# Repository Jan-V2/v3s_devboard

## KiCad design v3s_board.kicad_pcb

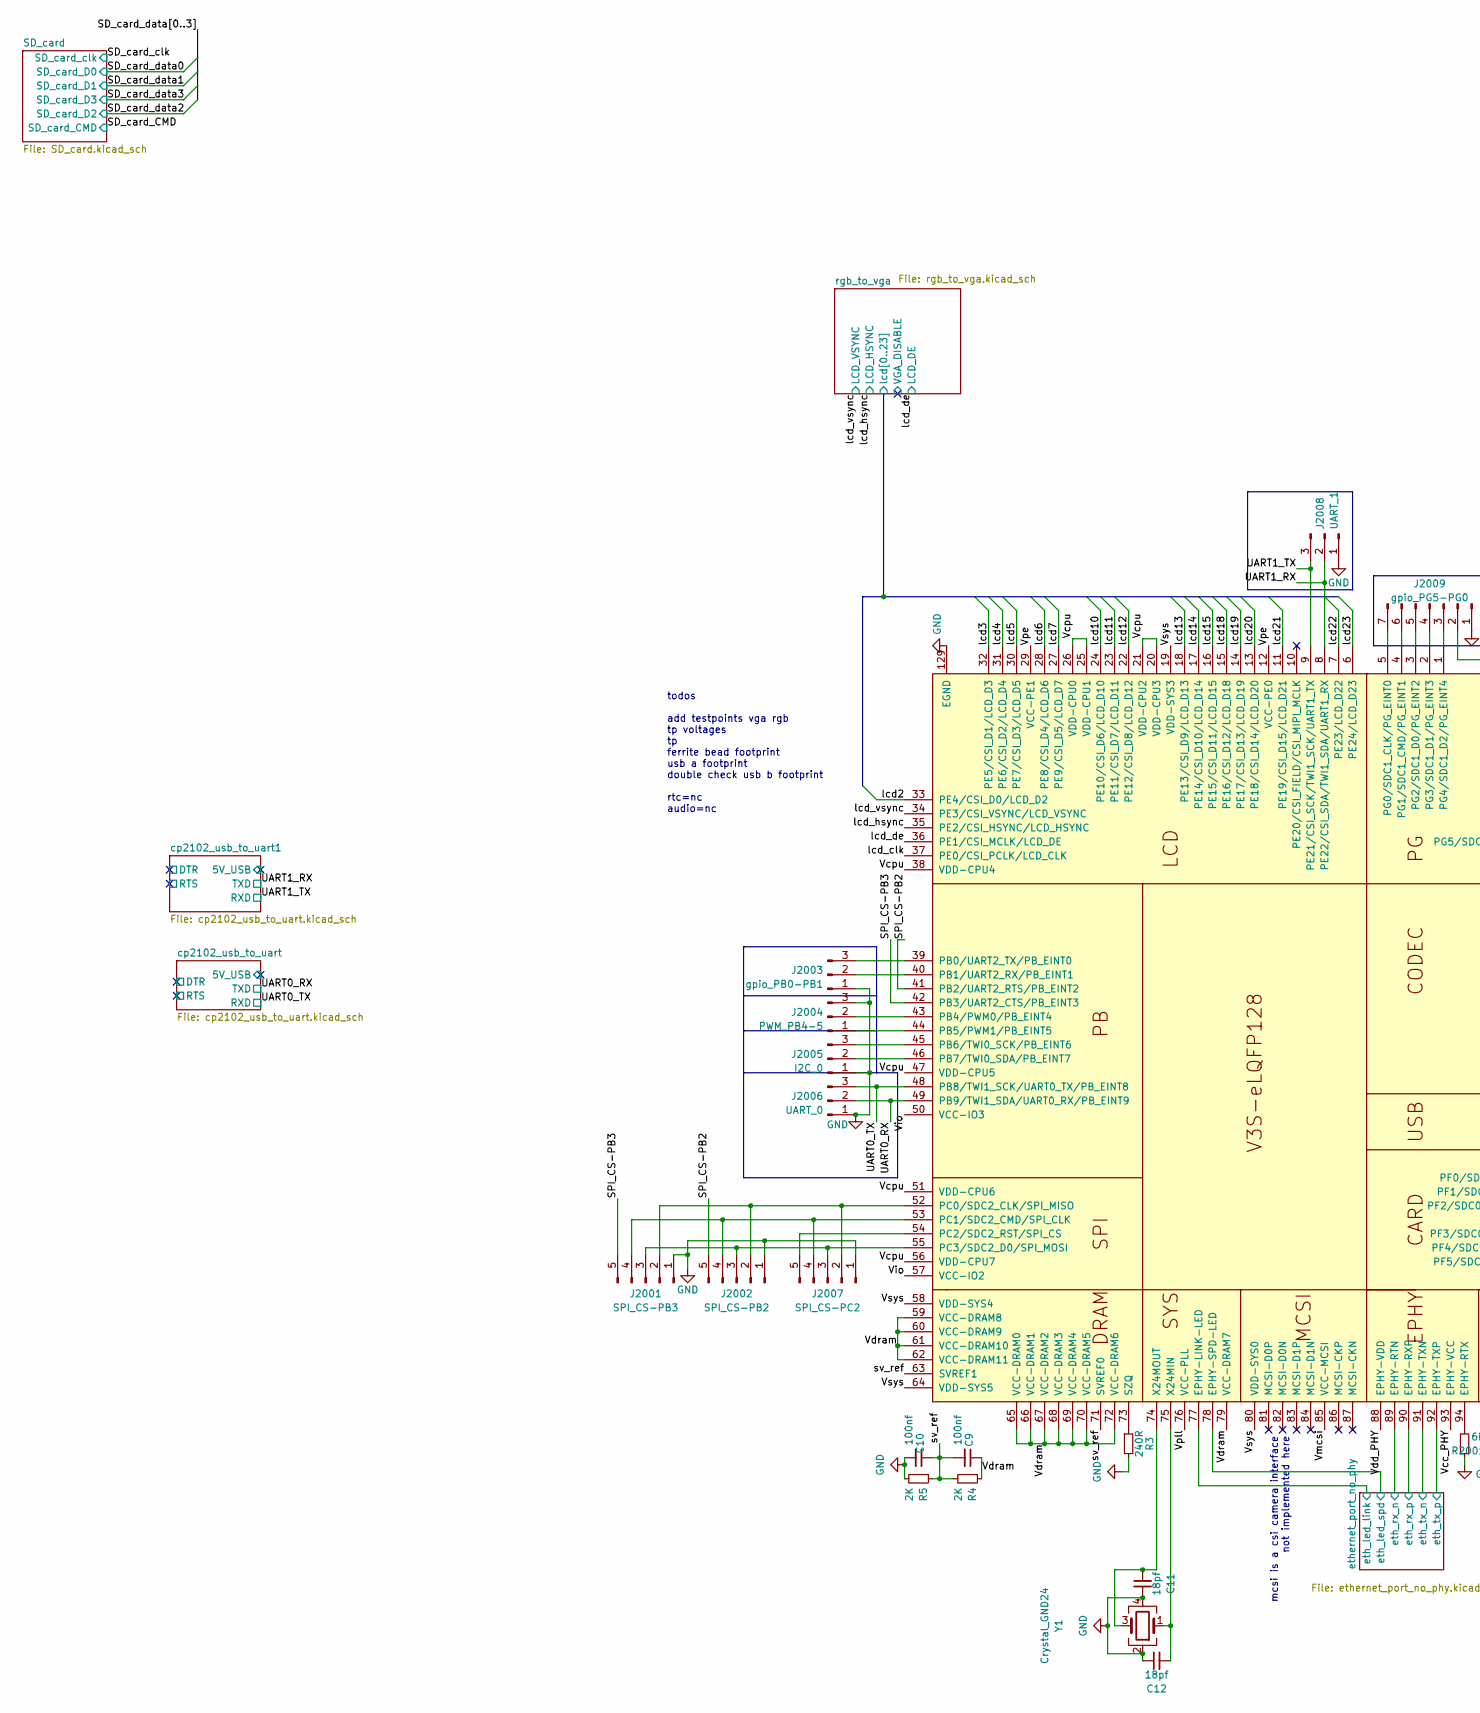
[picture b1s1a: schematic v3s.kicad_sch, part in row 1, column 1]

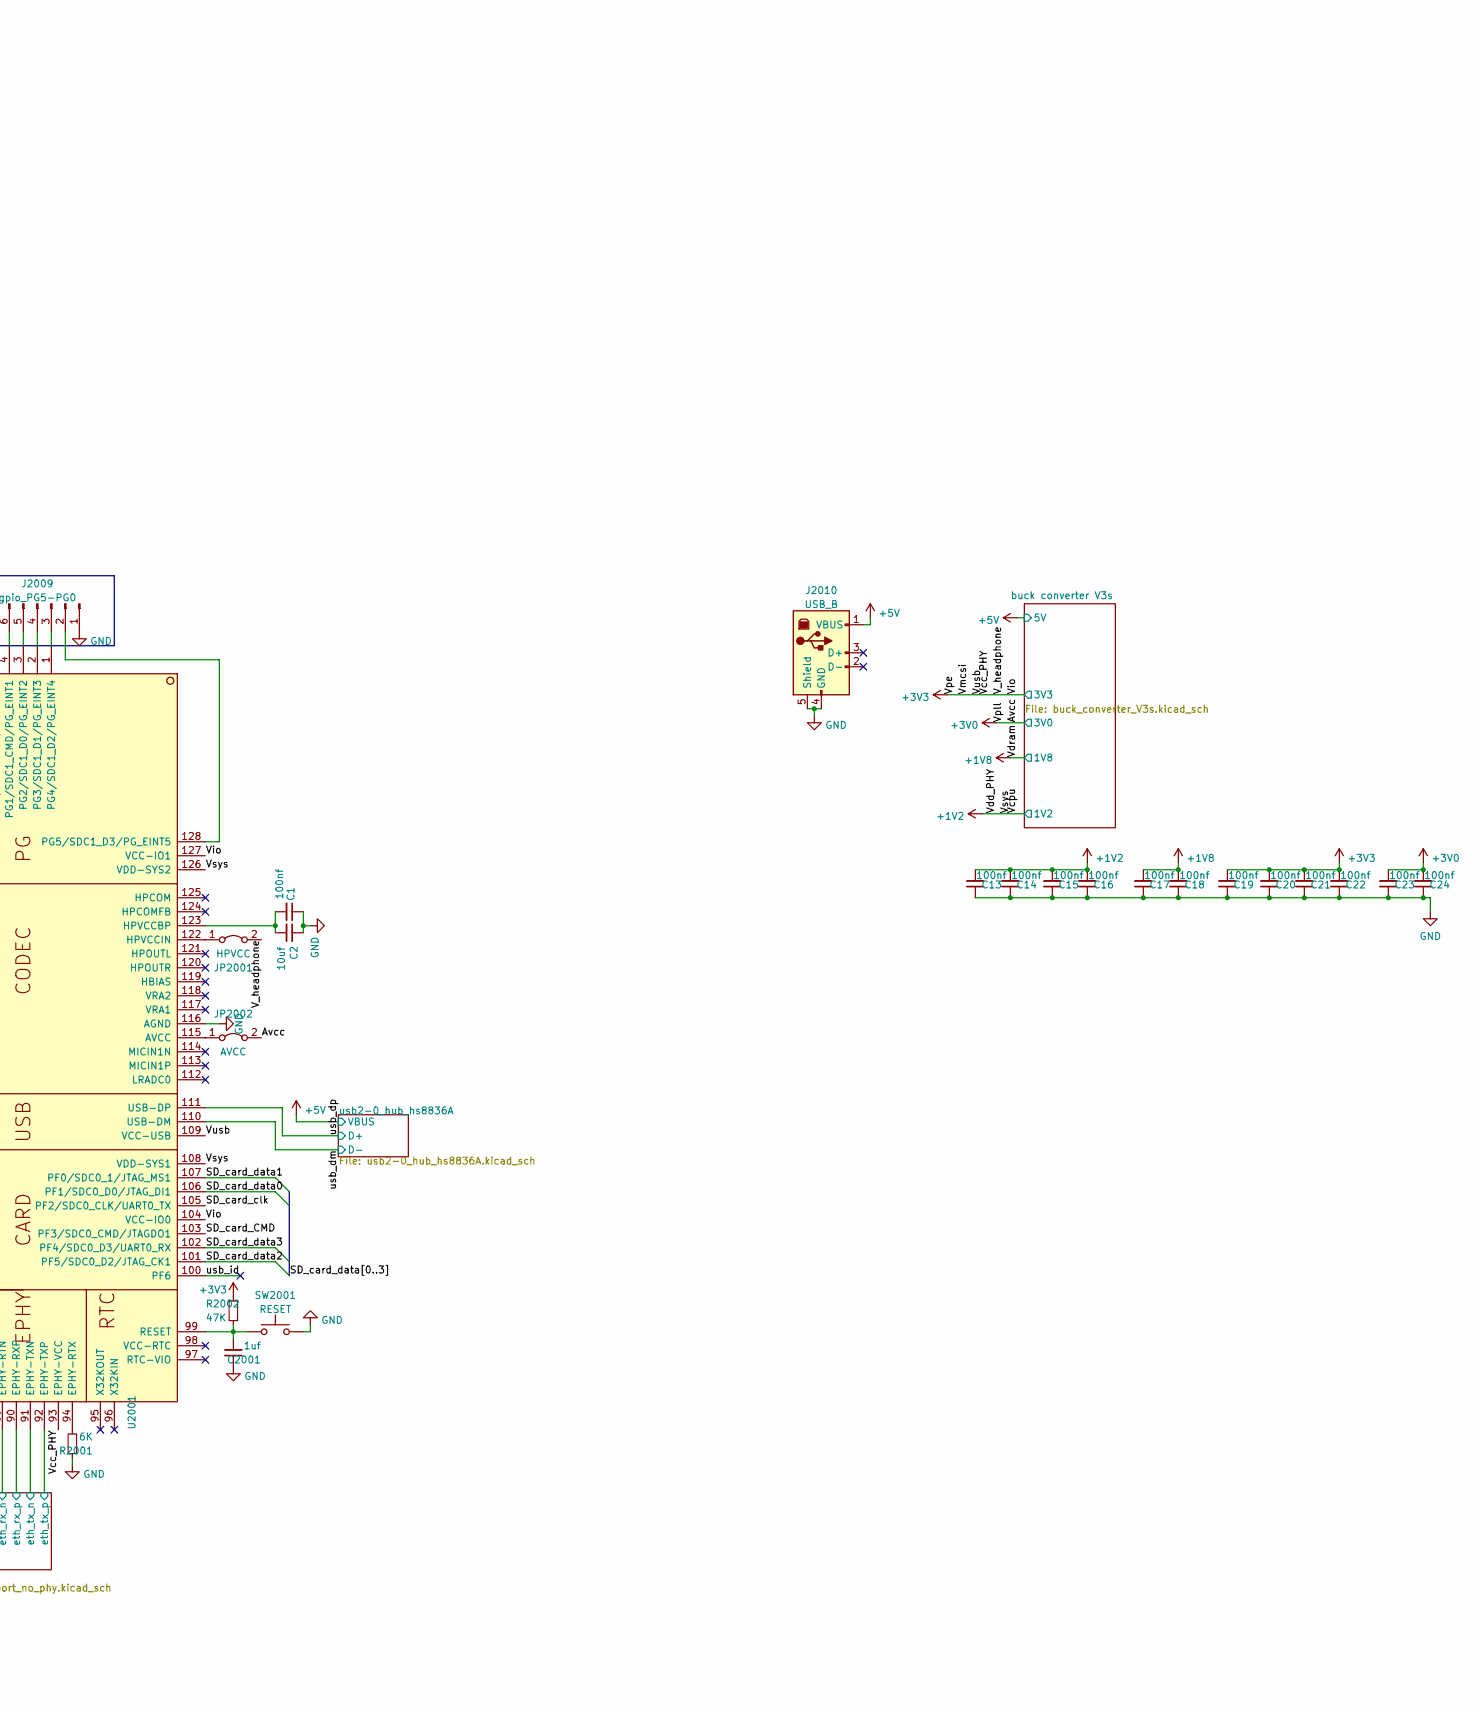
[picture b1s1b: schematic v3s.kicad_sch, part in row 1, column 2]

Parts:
C1, C9, C10, C13, C14, C15, C16, C17, C18, C19, C20, C21, C22, C23, C24: 100nf; C_0603_1608Metric
C2: 10uf; C_0603_1608Metric
C11, C12: 18pf; C_0603_1608Metric
C2001: 1uf; C_0603_1608Metric
J2001: SPI_CS-PB3; PinHeader_1x05_P2.54mm_Vertical
J2002: SPI_CS-PB2; PinHeader_1x05_P2.54mm_Vertical
J2003: gpio_PB0-PB1; PinHeader_1x03_P2.54mm_Vertical
J2004: PWM_PB4-5; PinHeader_1x03_P2.54mm_Vertical
J2005: I2C_0; PinHeader_1x03_P2.54mm_Vertical
J2006: UART_0; PinHeader_1x03_P2.54mm_Vertical
J2007: SPI_CS-PC2; PinHeader_1x05_P2.54mm_Vertical
J2008: UART_1; PinHeader_1x03_P2.54mm_Vertical
J2009: gpio_PG5-PG0; PinHeader_1x07_P2.54mm_Vertical
J2010: USB_B; USB_B_TE_5787834_Vertical
JP2001: HPVCC; SolderJumper-2_P1.3mm_Bridged_Pad1.0x1.5mm
JP2002: AVCC; SolderJumper-2_P1.3mm_Bridged_Pad1.0x1.5mm
R3: 240R; R_0603_1608Metric
R4, R5: 2K; R_0603_1608Metric
R2001: 6K; R_0603_1608Metric
R2002: 47K; R_0603_1608Metric
SW2001: RESET; SW_PUSH_6mm
U2001: V3S; LQFP-128_14x14mm_P0.4mm
Y1: Crystal_GND24; Crystal_SMD_3225-4Pin_3.2x2.5mm_HandSoldering

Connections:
+1V2: C13.2, C14.2, C15.2, C16.2, U2001.19 (VDD-SYS3), U2001.20 (VDD-CPU3), U2001.21 (VDD-CPU2), U2001.25 (VDD-CPU1), U2001.26 (VDD-CPU0), U2001.38 (VDD-CPU4), U2001.47 (VDD-CPU5), U2001.51 (VDD-CPU6), U2001.56 (VDD-CPU7), U2001.58 (VDD-SYS4), U2001.64 (VDD-SYS5), U2001.80 (VDD-SYS0), U2001.88 (EPHY-VDD), U2001.108 (VDD-SYS1), U2001.126 (VDD-SYS2); also elsewhere on the board
+1V8: C9.1, C17.2, C18.2, R4.1, U2001.59 (VCC-DRAM8), U2001.60 (VCC-DRAM9), U2001.61 (VCC-DRAM10), U2001.62 (VCC-DRAM11), U2001.65 (VCC-DRAM0), U2001.66 (VCC-DRAM1), U2001.67 (VCC-DRAM2), U2001.68 (VCC-DRAM3), U2001.69 (VCC-DRAM4), U2001.70 (VCC-DRAM5), U2001.72 (VCC-DRAM6), U2001.79 (VCC-DRAM7); also elsewhere on the board
+3V0: C23.2, C24.2, JP2002.2 (B), U2001.76 (VCC-PLL); also elsewhere on the board
+3V3: C19.2, C20.2, C21.2, C22.2, JP2001.2 (B), R2002.1, U2001.12 (VCC-PE0), U2001.29 (VCC-PE1), U2001.50 (VCC-IO3), U2001.57 (VCC-IO2), U2001.85 (VCC-MCSI), U2001.93 (EPHY-VCC), U2001.104 (VCC-IO0), U2001.109 (VCC-USB), U2001.127 (VCC-IO1); also elsewhere on the board
+5V: J2010.1 (VBUS); also elsewhere on the board
/v3s/SD_card_CMD: U2001.103 (PF3/SDC0_CMD/JTAGDO1); also elsewhere on the board
/v3s/SD_card_clk: U2001.105 (PF2/SDC0_CLK/UART0_TX); also elsewhere on the board
/v3s/SD_card_data0: U2001.106 (PF1/SDC0_D0/JTAG_DI1); also elsewhere on the board
/v3s/SD_card_data1: U2001.107 (PF0/SDC0_1/JTAG_MS1); also elsewhere on the board
/v3s/SD_card_data2: U2001.101 (PF5/SDC0_D2/JTAG_CK1); also elsewhere on the board
/v3s/SD_card_data3: U2001.102 (PF4/SDC0_D3/UART0_RX); also elsewhere on the board
/v3s/SPI_CS-PB2: J2002.5, U2001.41 (PB2/UART2_RTS/PB_EINT2)
/v3s/SPI_CS-PB3: J2001.5, U2001.42 (PB3/UART2_CTS/PB_EINT3)
/v3s/UART0_RX: J2006.2, U2001.49 (PB9/TWI1_SDA/UART0_RX/PB_EINT9); also elsewhere on the board
/v3s/UART0_TX: J2006.3, U2001.48 (PB8/TWI1_SCK/UART0_TX/PB_EINT8); also elsewhere on the board
/v3s/UART1_RX: J2008.2, U2001.8 (PE22/CSI_SDA/TWI1_SDA/UART1_RX); also elsewhere on the board
/v3s/UART1_TX: J2008.3, U2001.9 (PE21/CSI_SCK/TWI1_SCK/UART1_TX); also elsewhere on the board
/v3s/ethernet_port_no_phy/eth_led_link: U2001.77 (EPHY-LINK-LED); also elsewhere on the board
/v3s/ethernet_port_no_phy/eth_led_spd: U2001.78 (EPHY-SPD-LED); also elsewhere on the board
/v3s/ethernet_port_no_phy/eth_rx_n: U2001.89 (EPHY-RTN); also elsewhere on the board
/v3s/ethernet_port_no_phy/eth_rx_p: U2001.90 (EPHY-RXP); also elsewhere on the board
/v3s/ethernet_port_no_phy/eth_tx_n: U2001.91 (EPHY-TXN); also elsewhere on the board
/v3s/ethernet_port_no_phy/eth_tx_p: U2001.92 (EPHY-TXP); also elsewhere on the board
/v3s/lcd_clk: U2001.37 (PE0/CSI_PCLK/LCD_CLK)
/v3s/lcd_de: U2001.36 (PE1/CSI_MCLK/LCD_DE); also elsewhere on the board
/v3s/lcd_hsync: U2001.35 (PE2/CSI_HSYNC/LCD_HSYNC); also elsewhere on the board
/v3s/lcd_vsync: U2001.34 (PE3/CSI_VSYNC/LCD_VSYNC); also elsewhere on the board
/v3s/rgb_to_vga/lcd2: U2001.33 (PE4/CSI_D0/LCD_D2); also elsewhere on the board
/v3s/rgb_to_vga/lcd3: U2001.32 (PE5/CSI_D1/LCD_D3); also elsewhere on the board
/v3s/rgb_to_vga/lcd4: U2001.31 (PE6/CSI_D2/LCD_D4); also elsewhere on the board
/v3s/rgb_to_vga/lcd5: U2001.30 (PE7/CSI_D3/LCD_D5); also elsewhere on the board
/v3s/rgb_to_vga/lcd6: U2001.28 (PE8/CSI_D4/LCD_D6); also elsewhere on the board
/v3s/rgb_to_vga/lcd7: U2001.27 (PE9/CSI_D5/LCD_D7); also elsewhere on the board
/v3s/rgb_to_vga/lcd10: U2001.24 (PE10/CSI_D6/LCD_D10); also elsewhere on the board
/v3s/rgb_to_vga/lcd11: U2001.23 (PE11/CSI_D7/LCD_D11); also elsewhere on the board
/v3s/rgb_to_vga/lcd12: U2001.22 (PE12/CSI_D8/LCD_D12); also elsewhere on the board
/v3s/rgb_to_vga/lcd13: U2001.18 (PE13/CSI_D9/LCD_D13); also elsewhere on the board
/v3s/rgb_to_vga/lcd14: U2001.17 (PE14/CSI_D10/LCD_D14); also elsewhere on the board
/v3s/rgb_to_vga/lcd15: U2001.16 (PE15/CSI_D11/LCD_D15); also elsewhere on the board
/v3s/rgb_to_vga/lcd18: U2001.15 (PE16/CSI_D12/LCD_D18); also elsewhere on the board
/v3s/rgb_to_vga/lcd19: U2001.14 (PE17/CSI_D13/LCD_D19); also elsewhere on the board
/v3s/rgb_to_vga/lcd20: U2001.13 (PE18/CSI_D14/LCD_D20); also elsewhere on the board
/v3s/rgb_to_vga/lcd21: U2001.11 (PE19/CSI_D15/LCD_D21); also elsewhere on the board
/v3s/rgb_to_vga/lcd22: U2001.7 (PE23/LCD_D22); also elsewhere on the board
/v3s/rgb_to_vga/lcd23: U2001.6 (PE24/LCD_D23); also elsewhere on the board
/v3s/sv_ref: C9.2, C10.1, R4.2, R5.1, U2001.63 (SVREF1), U2001.71 (SVREF0)
/v3s/usb_dm: U2001.110 (USB-DM); also elsewhere on the board
/v3s/usb_dp: U2001.111 (USB-DP); also elsewhere on the board
/v3s/usb_id: U2001.100 (PF6)
GND: C1.1, C2.1, C10.2, C11.1, C12.1, C13.1, C14.1, C15.1, C16.1, C17.1, C18.1, C19.1, C20.1, C21.1, C22.1, C23.1, C24.1, C2001.1, J2001.1, J2002.1, J2003.1, J2004.3, J2005.1, J2006.1, J2007.1, J2008.1, J2009.1, J2010.4 (GND), J2010.5 (Shield), R3.2, R5.2, R2001.1, SW2001.2, U2001.116 (AGND), U2001.129 (EGND), Y1.2, Y1.4; also elsewhere on the board
unnamed: C1.2, C2.2, U2001.123 (HPVCCBP)
unnamed: C11.2, U2001.74 (X24MOUT), Y1.3
unnamed: C12.2, U2001.75 (X24MIN), Y1.1
unnamed: C2001.2, R2002.2, SW2001.1, U2001.99 (RESET)
unnamed: J2001.2, J2002.2, J2007.2, U2001.52 (PC0/SDC2_CLK/SPI_MISO)
unnamed: J2001.3, J2002.3, J2007.3, U2001.55 (PC3/SDC2_D0/SPI_MOSI)
unnamed: J2001.4, J2002.4, J2007.4, U2001.53 (PC1/SDC2_CMD/SPI_CLK)
unnamed: J2003.2, U2001.40 (PB1/UART2_RX/PB_EINT1)
unnamed: J2003.3, U2001.39 (PB0/UART2_TX/PB_EINT0)
unnamed: J2004.1, U2001.44 (PB5/PWM1/PB_EINT5)
unnamed: J2004.2, U2001.43 (PB4/PWM0/PB_EINT4)
unnamed: J2005.2, U2001.46 (PB7/TWI0_SDA/PB_EINT7)
unnamed: J2005.3, U2001.45 (PB6/TWI0_SCK/PB_EINT6)
unnamed: J2007.5, U2001.54 (PC2/SDC2_RST/SPI_CS)
unnamed: J2009.2, U2001.128 (PG5/SDC1_D3/PG_EINT5)
unnamed: J2009.3, U2001.1 (PG4/SDC1_D2/PG_EINT4)
unnamed: J2009.4, U2001.2 (PG3/SDC1_D1/PG_EINT3)
unnamed: J2009.5, U2001.3 (PG2/SDC1_D0/PG_EINT2)
unnamed: J2009.6, U2001.4 (PG1/SDC1_CMD/PG_EINT1)
unnamed: J2009.7, U2001.5 (PG0/SDC1_CLK/PG_EINT0)
unnamed: JP2001.1 (A), U2001.122 (HPVCCIN)
unnamed: JP2002.1 (A), U2001.115 (AVCC)
unnamed: R3.1, U2001.73 (SZQ)
unnamed: R2001.2, U2001.94 (EPHY-RTX)

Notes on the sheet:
todos add testpoints vga rgb tp voltages tp ferrite bead footprint usb a footprint double check usb b footprint rtc=nc audio=nc
mcsi is a csi camera interface not implemented here

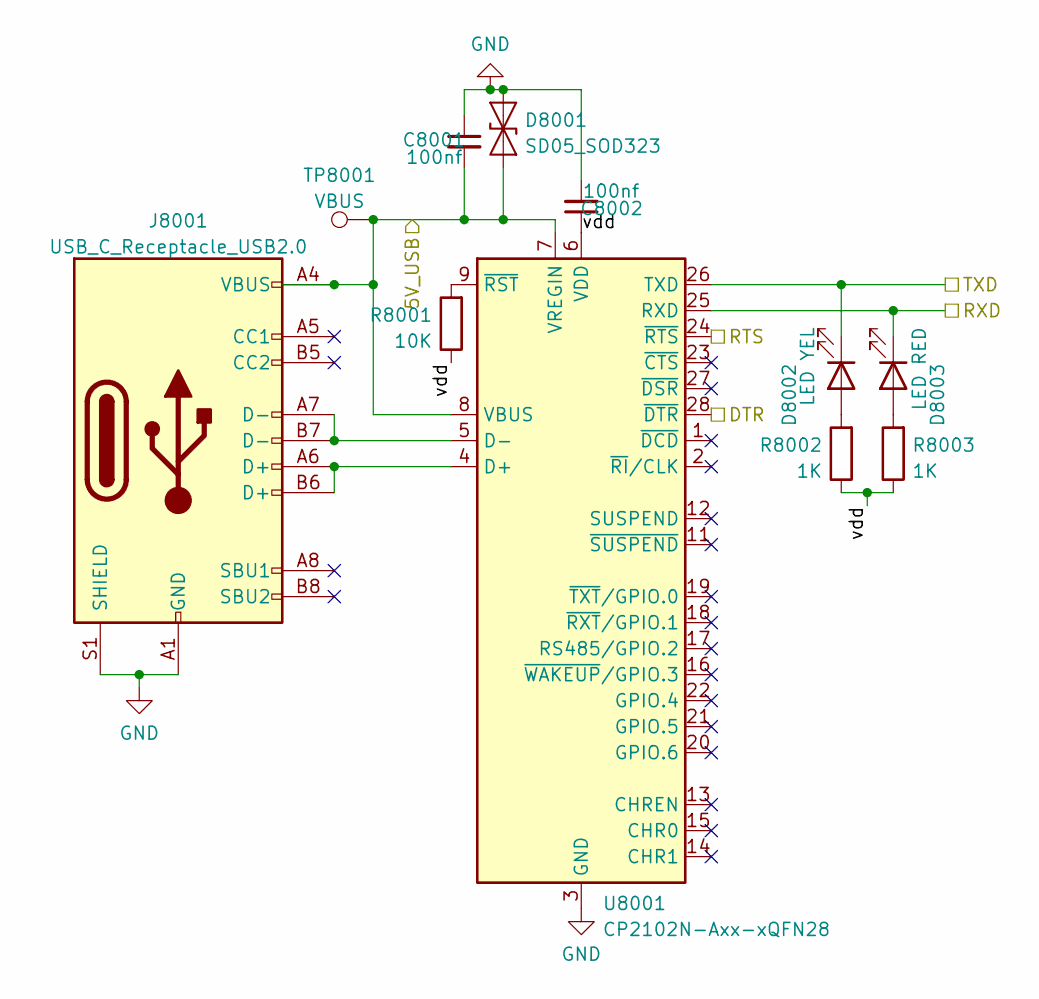
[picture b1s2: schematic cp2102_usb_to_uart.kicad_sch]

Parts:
C8001, C8002: 100nf; C_0603_1608Metric
D8001: SD05_SOD323; D_SOD-323
D8002: LED YEL; LED_0603_1608Metric
D8003: LED RED; LED_0603_1608Metric
J8001: USB_C_Receptacle_USB2.0; TYPE-C-31-M-14_top_mnt_usb2
R8001: 10K; R_0603_1608Metric
R8002, R8003: 1K; R_0603_1608Metric
TP8001: VBUS; TestPoint_Pad_D1.0mm
U8001: CP2102N-Axx-xQFN28; QFN-28-1EP_5x5mm_P0.5mm_EP3.35x3.35mm

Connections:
/v3s/UART1_RX: D8002.1 (K), U8001.26 (TXD); also elsewhere on the board
/v3s/UART1_TX: D8003.1 (K), U8001.25 (RXD); also elsewhere on the board
/v3s/cp2102_usb_to_uart1/5V_USB: C8001.2, D8001.1 (A1), J8001.A4 (VBUS), J8001.A9 (VBUS), J8001.B4 (VBUS), J8001.B9 (VBUS), TP8001.1, U8001.7 (VREGIN), U8001.8 (VBUS)
/v3s/cp2102_usb_to_uart1/DTR: U8001.28 (~DTR)
/v3s/cp2102_usb_to_uart1/RTS: U8001.24 (~RTS)
/v3s/cp2102_usb_to_uart1/vdd: C8002.1, R8001.1, R8002.1, R8003.1, U8001.6 (VDD)
GND: C8001.1, C8002.2, D8001.2 (A2), J8001.A1 (GND), J8001.A12 (GND), J8001.B1 (GND), J8001.B12 (GND), J8001.S1 (SHIELD), U8001.3 (GND), U8001.29 (GND); also elsewhere on the board
unnamed: D8002.2 (A), R8002.2
unnamed: D8003.2 (A), R8003.2
unnamed: J8001.A6 (D+), J8001.B6 (D+), U8001.4 (D+)
unnamed: J8001.A7 (D-), J8001.B7 (D-), U8001.5 (D-)
unnamed: R8001.2, U8001.9 (~RST)

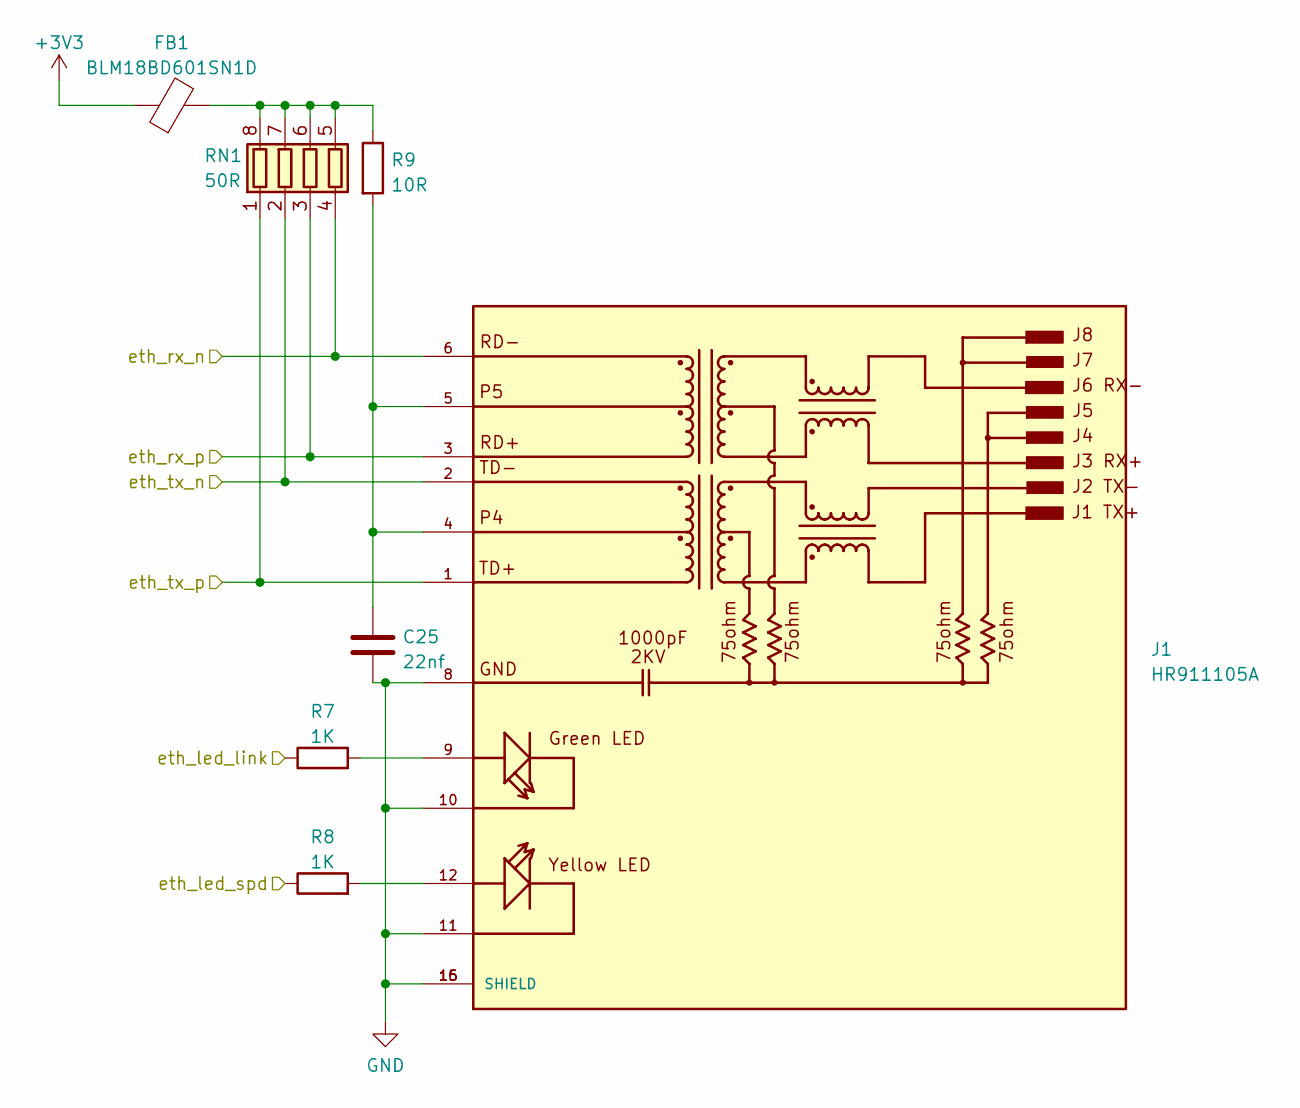
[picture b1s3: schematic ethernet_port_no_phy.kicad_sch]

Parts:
C25: 22nf; C_0603_1608Metric
FB1: BLM18BD601SN1D; C_0603_1608Metric
J1: HR911105A; HANRUN_HR911105A; PARTREV A
R7, R8: 1K; R_0603_1608Metric
R9: 10R; R_0603_1608Metric
RN1: 50R; R_Array_Concave_4x0603

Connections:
+3V3: FB1.1; also elsewhere on the board
/v3s/ethernet_port_no_phy/eth_led_link: R7.1; also elsewhere on the board
/v3s/ethernet_port_no_phy/eth_led_spd: R8.1; also elsewhere on the board
/v3s/ethernet_port_no_phy/eth_rx_n: J1.6, RN1.4 (R4.1); also elsewhere on the board
/v3s/ethernet_port_no_phy/eth_rx_p: J1.3, RN1.3 (R3.1); also elsewhere on the board
/v3s/ethernet_port_no_phy/eth_tx_n: J1.2, RN1.2 (R2.1); also elsewhere on the board
/v3s/ethernet_port_no_phy/eth_tx_p: J1.1, RN1.1 (R1.1); also elsewhere on the board
GND: C25.2, J1.8, J1.10, J1.11, J1.15 (SHIELD), J1.16 (SHIELD); also elsewhere on the board
unnamed: C25.1, J1.4, J1.5, R9.2
unnamed: FB1.2, R9.1, RN1.5 (R4.2), RN1.6 (R3.2), RN1.7 (R2.2), RN1.8 (R1.2)
unnamed: J1.9, R7.2
unnamed: J1.12, R8.2

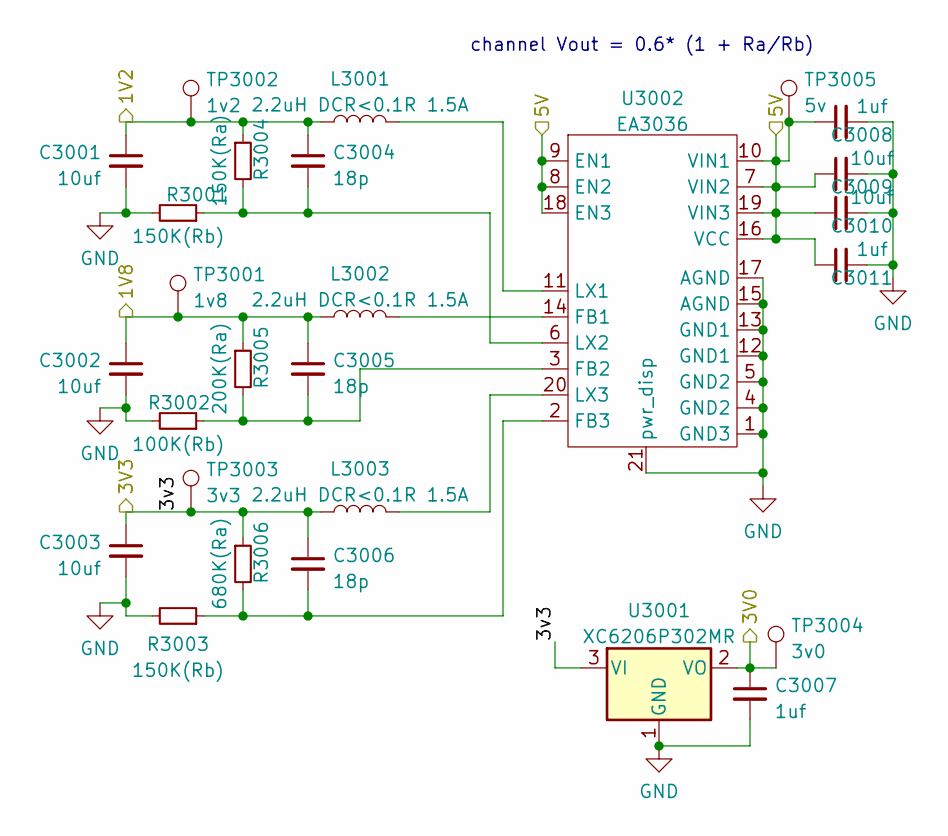
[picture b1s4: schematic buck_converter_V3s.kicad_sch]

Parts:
C3001, C3002, C3003, C3009, C3010: 10uf; C_0603_1608Metric
C3004, C3005, C3006: 18p; C_0603_1608Metric
C3007, C3008, C3011: 1uf; C_0603_1608Metric
L3001, L3002, L3003: 2.2uH DCR<0.1R 1.5A; L_1210_3225Metric
R3001, R3003: 150K(Rb); R_0603_1608Metric
R3002: 100K(Rb); R_0603_1608Metric
R3004: 150K(Ra); R_0603_1608Metric
R3005: 200K(Ra); R_0603_1608Metric
R3006: 680K(Ra); R_0603_1608Metric
TP3001: 1v8; TestPoint_Pad_D1.0mm
TP3002: 1v2; TestPoint_Pad_D1.0mm
TP3003: 3v3; TestPoint_Pad_D1.0mm
TP3004: 3v0; TestPoint_Pad_D1.0mm
TP3005: 5v; TestPoint_Pad_D1.0mm
U3001: XC6206P302MR; SOT-23
U3002: EA3036; QFN-20-1EP_3x3mm_P0.4mm_EP1.65x1.65mm

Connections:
+1V2: C3001.1, C3004.1, L3001.1, R3004.1, TP3002.1; also elsewhere on the board
+1V8: C3002.1, C3005.1, L3002.1, R3005.1, TP3001.1; also elsewhere on the board
+3V0: C3007.1, TP3004.1, U3001.2 (VO); also elsewhere on the board
+3V3: C3003.1, C3006.1, L3003.1, R3006.1, TP3003.1, U3001.3 (VI); also elsewhere on the board
+5V: C3008.1, C3009.1, C3010.1, C3011.1, TP3005.1, U3002.7 (VIN2), U3002.8 (EN2), U3002.9 (EN1), U3002.10 (VIN1), U3002.16 (VCC), U3002.18 (EN3), U3002.19 (VIN3); also elsewhere on the board
GND: C3001.2, C3002.2, C3003.2, C3007.2, C3008.2, C3009.2, C3010.2, C3011.2, R3001.2, R3002.2, R3003.2, U3001.1 (GND), U3002.1 (GND3), U3002.4 (GND2), U3002.5 (GND2), U3002.12 (GND1), U3002.13 (GND1), U3002.15 (AGND), U3002.17 (AGND), U3002.21 (pwr_disp); also elsewhere on the board
unnamed: C3004.2, R3001.1, R3004.2, U3002.6 (LX2)
unnamed: C3005.2, R3002.1, R3005.2, U3002.3 (FB2)
unnamed: C3006.2, R3003.1, R3006.2, U3002.2 (FB3)
unnamed: L3001.2, U3002.11 (LX1)
unnamed: L3002.2, U3002.14 (FB1)
unnamed: L3003.2, U3002.20 (LX3)

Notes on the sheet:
channel Vout = 0.6* (1 + Ra/Rb)

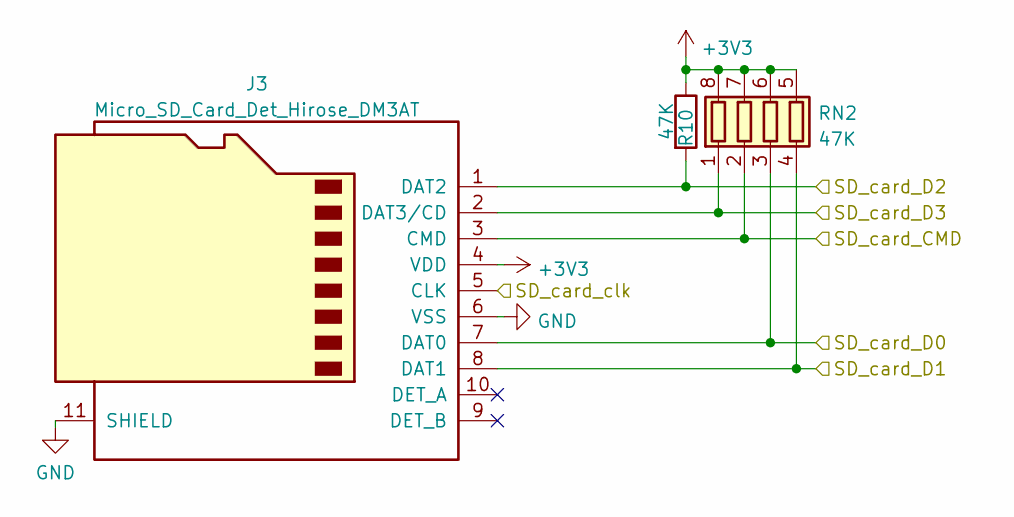
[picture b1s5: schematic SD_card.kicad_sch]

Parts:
J3: Micro_SD_Card_Det_Hirose_DM3AT; microSD_HC_Hirose_DM3AT-SF-PEJM5
R10: 47K; R_0603_1608Metric
RN2: 47K; R_Array_Concave_4x0603

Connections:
+3V3: J3.4 (VDD), R10.1, RN2.5 (R4.2), RN2.6 (R3.2), RN2.7 (R2.2), RN2.8 (R1.2); also elsewhere on the board
/v3s/SD_card_CMD: J3.3 (CMD), RN2.2 (R2.1); also elsewhere on the board
/v3s/SD_card_clk: J3.5 (CLK); also elsewhere on the board
/v3s/SD_card_data0: J3.7 (DAT0), RN2.3 (R3.1); also elsewhere on the board
/v3s/SD_card_data1: J3.8 (DAT1), RN2.4 (R4.1); also elsewhere on the board
/v3s/SD_card_data2: J3.1 (DAT2), R10.2; also elsewhere on the board
/v3s/SD_card_data3: J3.2 (DAT3/CD), RN2.1 (R1.1); also elsewhere on the board
GND: J3.6 (VSS), J3.11 (SHIELD); also elsewhere on the board

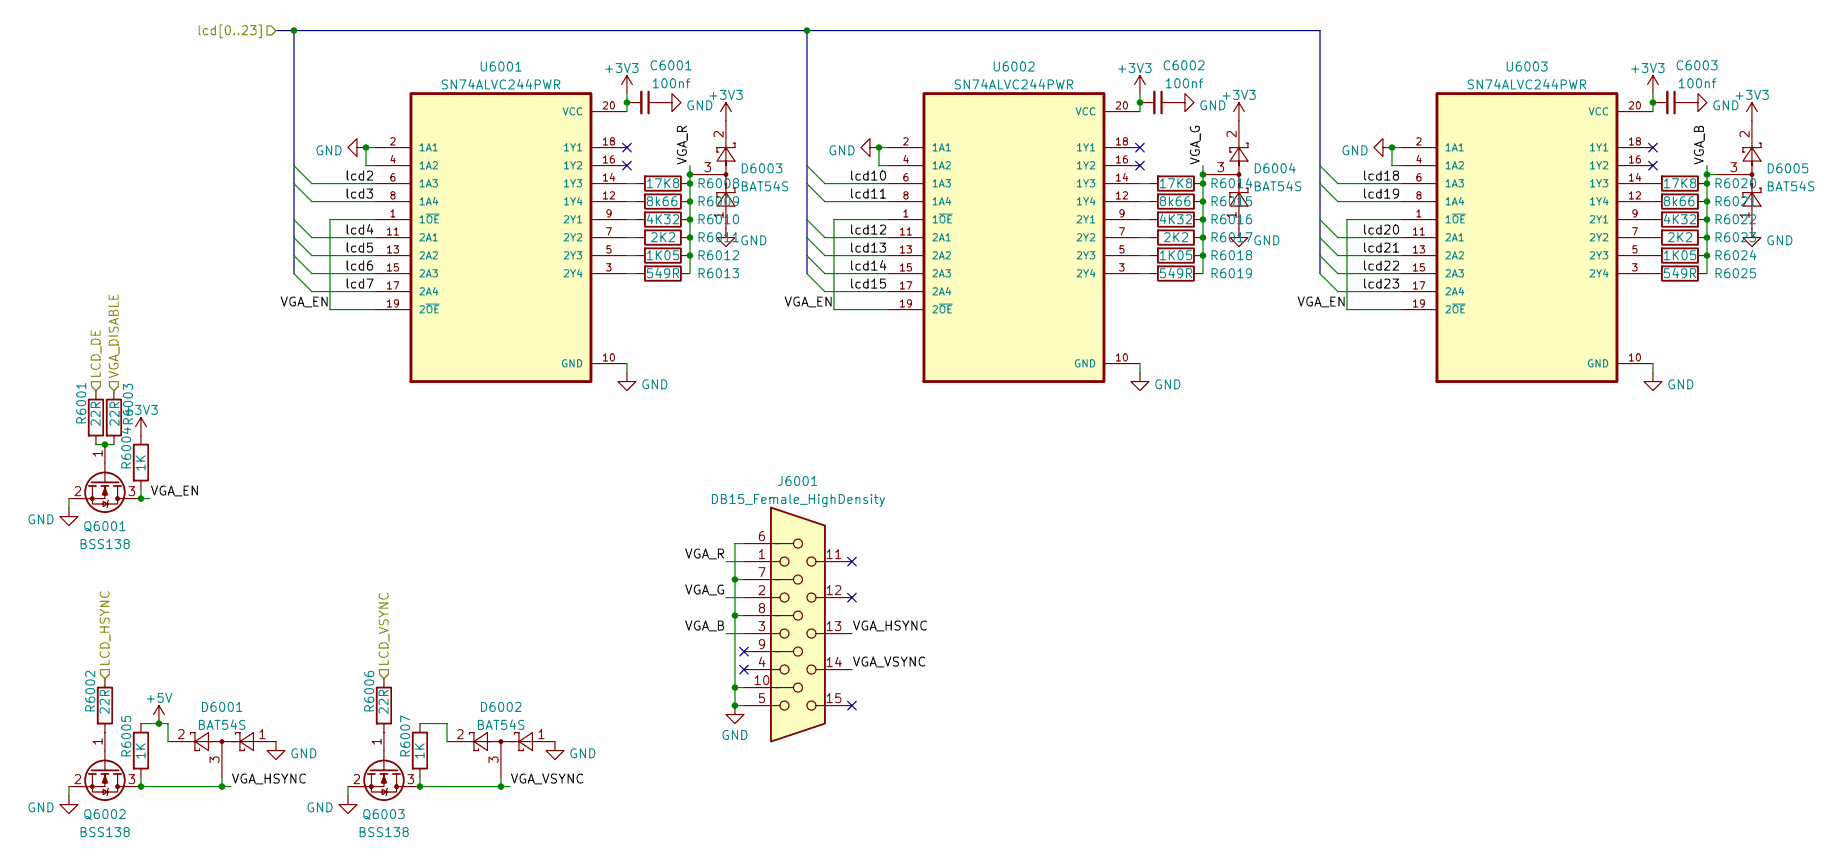
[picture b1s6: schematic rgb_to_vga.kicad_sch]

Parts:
C6001, C6002, C6003: 100nf; C_0603_1608Metric
D6001, D6002, D6003, D6004, D6005: BAT54S; SOT-23
J6001: DB15_Female_HighDensity; DSUB-15-HD_Female_Horizontal_P2.29x1.98mm_EdgePinOffset3.03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
Q6001, Q6002, Q6003: BSS138; SOT-23
R6001, R6002, R6003, R6006: 22R; R_0603_1608Metric
R6004, R6005, R6007: 1K; R_0603_1608Metric
R6008, R6014, R6020: 17K8; R_0402_1005Metric
R6009, R6015, R6021: 8k66; R_0402_1005Metric
R6010, R6016, R6022: 4K32; R_0402_1005Metric
R6011, R6017, R6023: 2K2; R_0402_1005Metric
R6012, R6018, R6024: 1K05; R_0402_1005Metric
R6013, R6019, R6025: 549R; R_0402_1005Metric
U6001, U6002, U6003: SN74ALVC244PWR; SOP-20_7.5x12.8mm_P1.27mm

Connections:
+3V3: C6001.2, C6002.2, C6003.2, D6003.2, D6004.2, D6005.2, R6004.1, U6001.20 (VCC), U6002.20 (VCC), U6003.20 (VCC); also elsewhere on the board
+5V: D6001.2, R6005.1; also elsewhere on the board
/v3s/lcd_de: R6001.1; also elsewhere on the board
/v3s/lcd_hsync: R6002.1; also elsewhere on the board
/v3s/lcd_vsync: R6006.1; also elsewhere on the board
/v3s/rgb_to_vga/VGA_B: D6005.3, J6001.3, R6020.1, R6021.1, R6022.1, R6023.1, R6024.1, R6025.1
/v3s/rgb_to_vga/VGA_DISABLE: R6003.1
/v3s/rgb_to_vga/VGA_EN: Q6001.3 (D), R6004.2, U6001.1 (1~OE), U6001.19 (2~OE), U6002.1 (1~OE), U6002.19 (2~OE), U6003.1 (1~OE), U6003.19 (2~OE)
/v3s/rgb_to_vga/VGA_G: D6004.3, J6001.2, R6014.1, R6015.1, R6016.1, R6017.1, R6018.1, R6019.1
/v3s/rgb_to_vga/VGA_HSYNC: D6001.3, J6001.13, Q6002.3 (D), R6005.2
/v3s/rgb_to_vga/VGA_R: D6003.3, J6001.1, R6008.1, R6009.1, R6010.1, R6011.1, R6012.1, R6013.1
/v3s/rgb_to_vga/VGA_VSYNC: D6002.3, J6001.14, Q6003.3 (D), R6007.2
/v3s/rgb_to_vga/lcd2: U6001.6 (1A3); also elsewhere on the board
/v3s/rgb_to_vga/lcd3: U6001.8 (1A4); also elsewhere on the board
/v3s/rgb_to_vga/lcd4: U6001.11 (2A1); also elsewhere on the board
/v3s/rgb_to_vga/lcd5: U6001.13 (2A2); also elsewhere on the board
/v3s/rgb_to_vga/lcd6: U6001.15 (2A3); also elsewhere on the board
/v3s/rgb_to_vga/lcd7: U6001.17 (2A4); also elsewhere on the board
/v3s/rgb_to_vga/lcd10: U6002.6 (1A3); also elsewhere on the board
/v3s/rgb_to_vga/lcd11: U6002.8 (1A4); also elsewhere on the board
/v3s/rgb_to_vga/lcd12: U6002.11 (2A1); also elsewhere on the board
/v3s/rgb_to_vga/lcd13: U6002.13 (2A2); also elsewhere on the board
/v3s/rgb_to_vga/lcd14: U6002.15 (2A3); also elsewhere on the board
/v3s/rgb_to_vga/lcd15: U6002.17 (2A4); also elsewhere on the board
/v3s/rgb_to_vga/lcd18: U6003.6 (1A3); also elsewhere on the board
/v3s/rgb_to_vga/lcd19: U6003.8 (1A4); also elsewhere on the board
/v3s/rgb_to_vga/lcd20: U6003.11 (2A1); also elsewhere on the board
/v3s/rgb_to_vga/lcd21: U6003.13 (2A2); also elsewhere on the board
/v3s/rgb_to_vga/lcd22: U6003.15 (2A3); also elsewhere on the board
/v3s/rgb_to_vga/lcd23: U6003.17 (2A4); also elsewhere on the board
GND: C6001.1, C6002.1, C6003.1, D6001.1, D6002.1, D6003.1, D6004.1, D6005.1, J6001.5, J6001.6, J6001.7, J6001.8, J6001.10, Q6001.2 (S), Q6002.2 (S), Q6003.2 (S), U6001.2 (1A1), U6001.4 (1A2), U6001.10 (GND), U6002.2 (1A1), U6002.4 (1A2), U6002.10 (GND), U6003.2 (1A1), U6003.4 (1A2), U6003.10 (GND); also elsewhere on the board
unnamed: D6002.2, R6007.1
unnamed: Q6001.1 (G), R6001.2, R6003.2
unnamed: Q6002.1 (G), R6002.2
unnamed: Q6003.1 (G), R6006.2
unnamed: R6008.2, U6001.14 (1Y3)
unnamed: R6009.2, U6001.12 (1Y4)
unnamed: R6010.2, U6001.9 (2Y1)
unnamed: R6011.2, U6001.7 (2Y2)
unnamed: R6012.2, U6001.5 (2Y3)
unnamed: R6013.2, U6001.3 (2Y4)
unnamed: R6014.2, U6002.14 (1Y3)
unnamed: R6015.2, U6002.12 (1Y4)
unnamed: R6016.2, U6002.9 (2Y1)
unnamed: R6017.2, U6002.7 (2Y2)
unnamed: R6018.2, U6002.5 (2Y3)
unnamed: R6019.2, U6002.3 (2Y4)
unnamed: R6020.2, U6003.14 (1Y3)
unnamed: R6021.2, U6003.12 (1Y4)
unnamed: R6022.2, U6003.9 (2Y1)
unnamed: R6023.2, U6003.7 (2Y2)
unnamed: R6024.2, U6003.5 (2Y3)
unnamed: R6025.2, U6003.3 (2Y4)

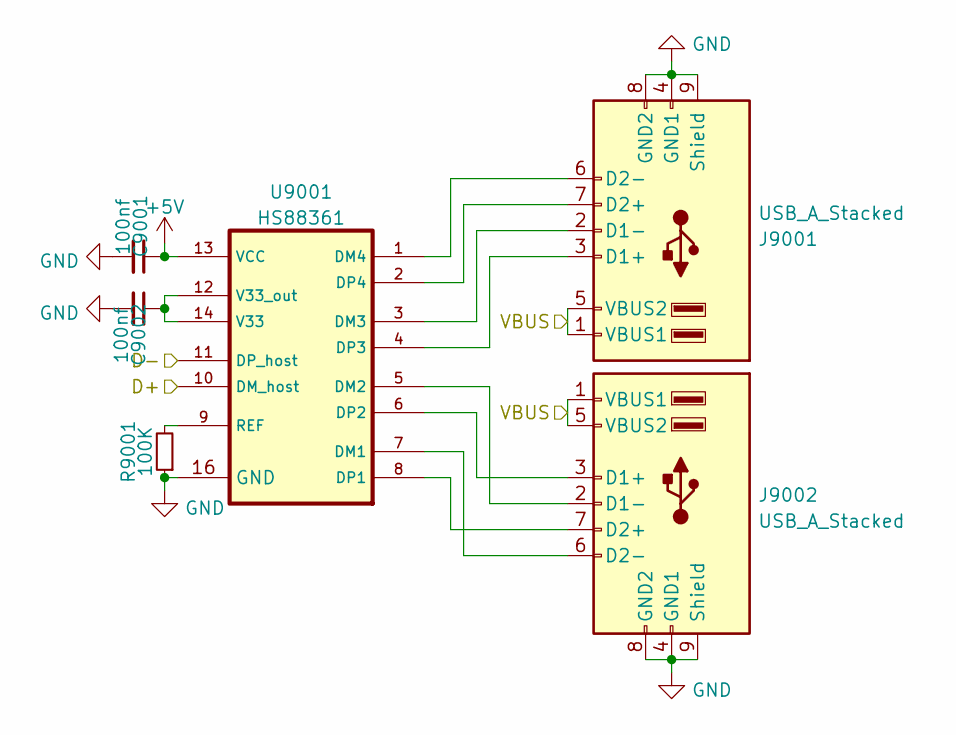
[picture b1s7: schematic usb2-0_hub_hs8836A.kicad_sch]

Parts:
C9001, C9002: 100nf; C_0603_1608Metric
J9001, J9002: USB_A_Stacked; USB_A_Wuerth_61400826021_Horizontal_Stacked
R9001: 100K; R_0603_1608Metric
U9001: HS88361; SO-16_3.9x9.9mm_P1.27mm

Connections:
+5V: C9001.1, J9001.1 (VBUS1), J9001.5 (VBUS2), J9002.1 (VBUS1), J9002.5 (VBUS2), U9001.13 (VCC); also elsewhere on the board
/v3s/usb_dm: U9001.11 (DP_host); also elsewhere on the board
/v3s/usb_dp: U9001.10 (DM_host); also elsewhere on the board
GND: C9001.2, C9002.2, J9001.4 (GND1), J9001.8 (GND2), J9001.9 (Shield), J9002.4 (GND1), J9002.8 (GND2), J9002.9 (Shield), R9001.1, U9001.16 (GND); also elsewhere on the board
unnamed: C9002.1, U9001.12 (V33_out), U9001.14 (V33)
unnamed: J9001.2 (D1-), U9001.3 (DM3)
unnamed: J9001.3 (D1+), U9001.4 (DP3)
unnamed: J9001.6 (D2-), U9001.1 (DM4)
unnamed: J9001.7 (D2+), U9001.2 (DP4)
unnamed: J9002.2 (D1-), U9001.5 (DM2)
unnamed: J9002.3 (D1+), U9001.6 (DP2)
unnamed: J9002.6 (D2-), U9001.7 (DM1)
unnamed: J9002.7 (D2+), U9001.8 (DP1)
unnamed: R9001.2, U9001.9 (REF)
